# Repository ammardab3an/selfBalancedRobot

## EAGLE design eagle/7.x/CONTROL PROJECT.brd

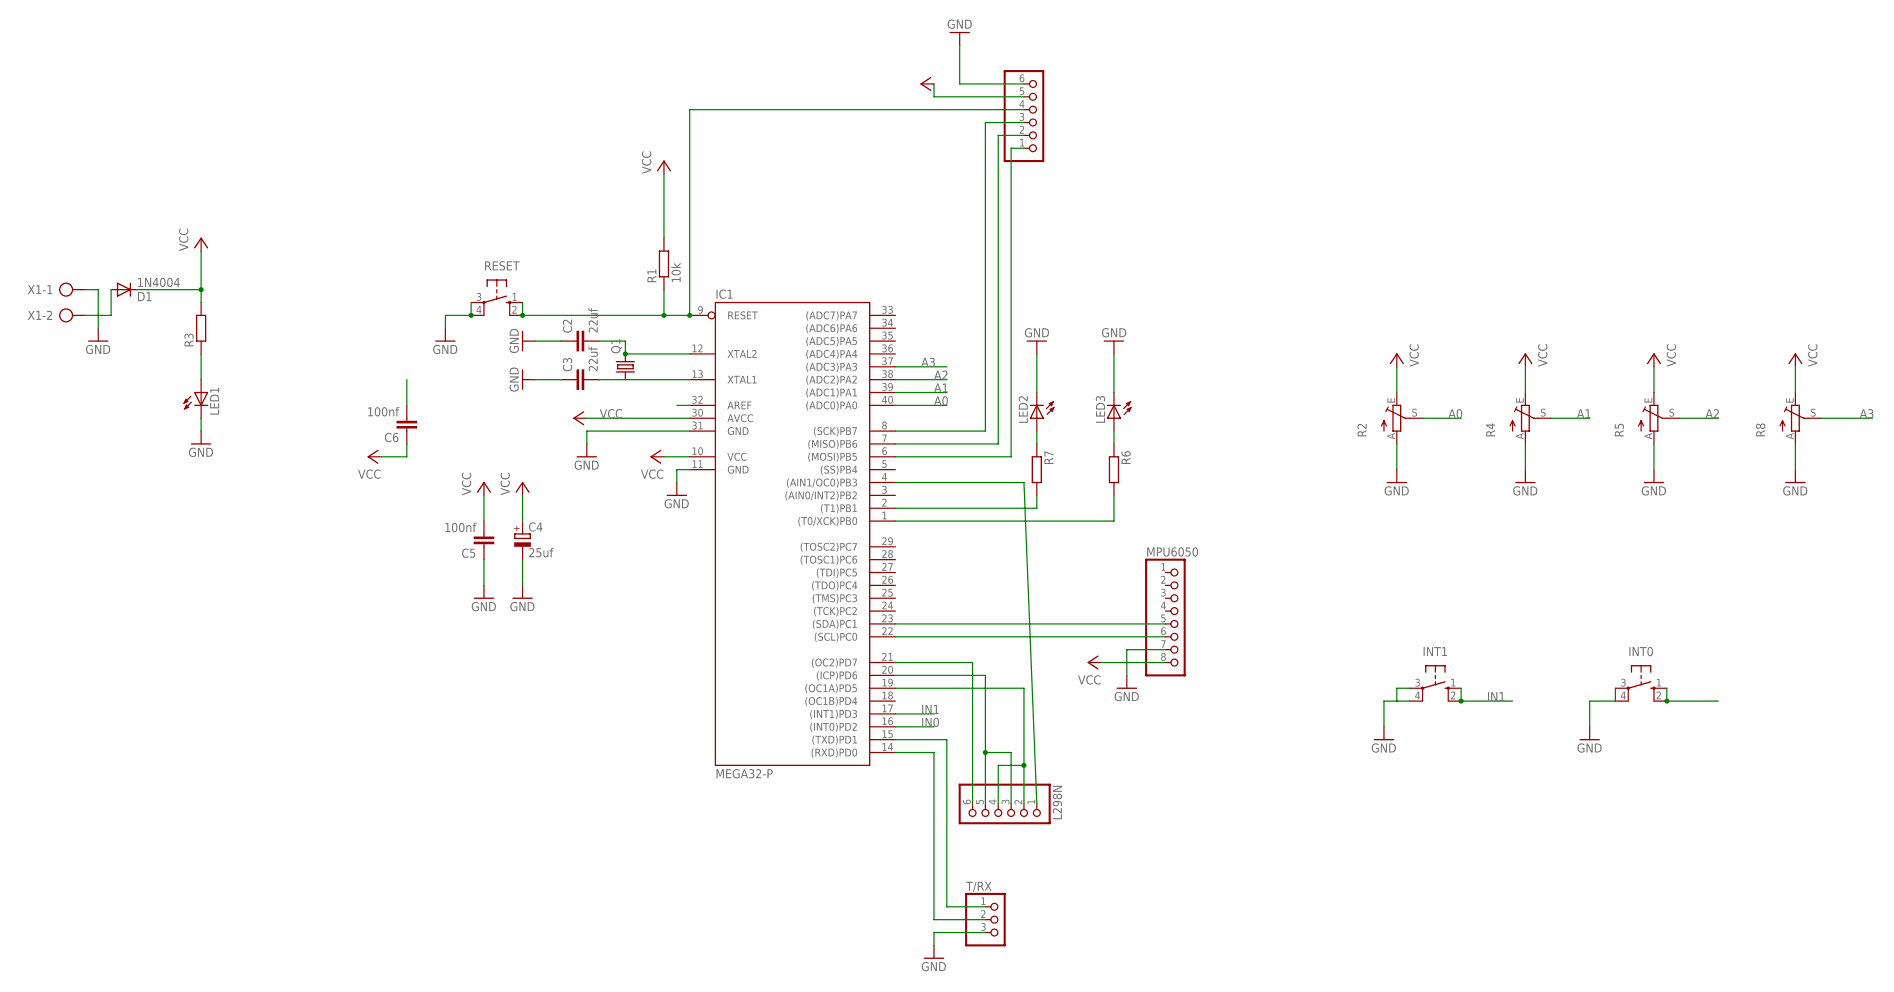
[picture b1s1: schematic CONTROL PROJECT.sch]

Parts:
C2, C3: 22uf; C050-025X075
C4: 25uf; E1,8-4
C5, C6: 100nf; C050-025X075
D1: 1N4004; DO41-10
IC1: MEGA32-P; DIL40
INT0, INT1: 10-XX; B3F-10XX
L298N: PINHD-1X6; 1X06
LED1, LED2, LED3: LED5MM
MPU6050: PINHD-1X8; 1X08
PROG: PINHD-1X6; 1X06
Q1: CRYSTALHC49U-V; HC49U-V
R1: 10k; 0207/7
R2, R4, R5, R8: TRIM_EU-RJ6; RJ6
R3, R6, R7: R-EU_0207/7; 0207/7
RESET: 10-XX; B3F-10XX
T/RX: PINHD-1X3; 1X03
X1: AK300/2

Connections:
A0: IC1.40 ((ADC0)PA0), R2.S
A1: IC1.39 ((ADC1)PA1), R4.S
A2: IC1.38 ((ADC2)PA2), R5.S
A3: IC1.37 ((ADC3)PA3), R8.S
AREF: C6.2, IC1.32 (AREF)
GND: C2.1, C3.1, C4.-, C5.1, IC1.11 (GND), IC1.31 (GND), INT0.3, INT0.4 (P1), INT1.3, INT1.4 (P1), LED1.K (C), LED2.K (C), LED3.K (C), MPU6050.7, PROG.6, R2.A, R4.A, R5.A, R8.A, RESET.3, RESET.4 (P1), T/RX.3, X1.1
IN0: IC1.16 ((INT0)PD2), INT0.1 (S), INT0.2 (S1)
IN1: IC1.17 ((INT1)PD3), INT1.1 (S), INT1.2 (S1)
MISO: IC1.7 ((MISO)PB6), PROG.2
MOSI: IC1.6 ((MOSI)PB5), PROG.1
unnamed: C2.2, IC1.12 (XTAL2), Q1.2
unnamed: C3.2, IC1.13 (XTAL1), Q1.1
unnamed: IC1.2 ((T1)PB1), R7.2
unnamed: LED1.A, R3.1
unnamed: D1.A, X1.2
unnamed: IC1.1 ((T0/XCK)PB0), R6.2
unnamed: LED3.A, R6.1
unnamed: LED2.A, R7.1
unnamed: IC1.19 ((OC1A)PD5), L298N.2, L298N.4
unnamed: IC1.20 ((ICP)PD6), L298N.3, L298N.5
OC0: IC1.4 ((AIN1/OC0)PB3), L298N.1
OC2: IC1.21 ((OC2)PD7), L298N.6
RESET: IC1.9 (RESET), PROG.4, R1.1, RESET.1 (S), RESET.2 (S1)
RX: IC1.14 ((RXD)PD0), T/RX.2
SCK: IC1.8 ((SCK)PB7), PROG.3
SCL: IC1.22 ((SCL)PC0), MPU6050.6
SDA: IC1.23 ((SDA)PC1), MPU6050.5
TX: IC1.15 ((TXD)PD1), T/RX.1
VCC: C4.+, C5.2, C6.1, D1.C, IC1.10 (VCC), IC1.30 (AVCC), MPU6050.8, PROG.5, R1.2, R2.E, R3.2, R4.E, R5.E, R8.E

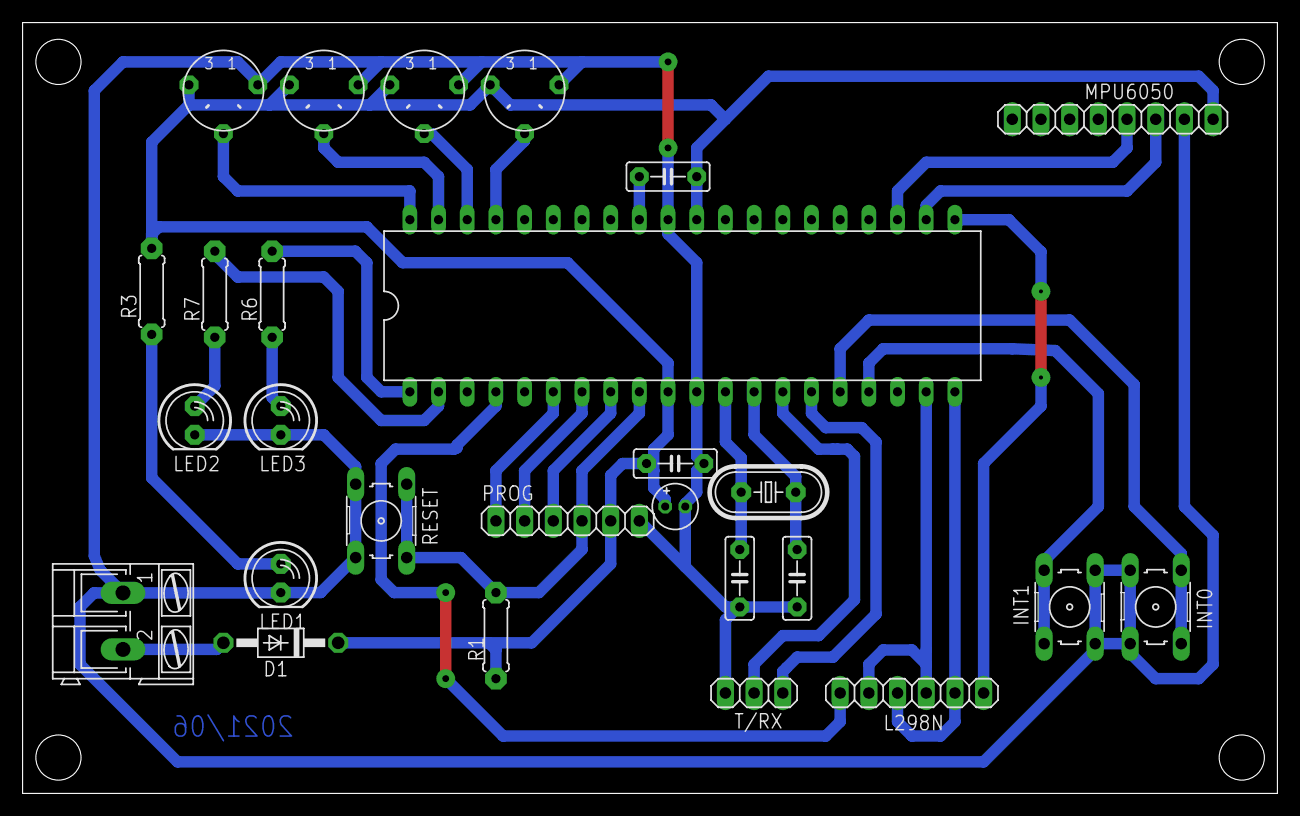
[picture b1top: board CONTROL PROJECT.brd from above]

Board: 2 copper layers, 111.1 x 68.2 mm, 27 parts (0 on the bottom side), 29 nets.

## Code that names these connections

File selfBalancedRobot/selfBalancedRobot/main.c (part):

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{
	TCNT0 = 0x00;
	TCNT2 = 0X00;
	DDRB |= 1 << PB3;
	DDRD |= 1 << PD7;
}

void PWM_Start()
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int main()
{
	
	DDRB |= (1<<PB0) | (1<<PB1);
	DDRD |= (1<<PD5) | (1<<PD6);
	
	I2C_Init();
	USART_Init(57600);
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		
		if(!go_flag || (pitch > 50) || (pitch < -50) || (roll > 50) || (roll < -50)){
			PWM_SetDutyCycle(0);
			PORTB |= (1<<PB1);
			PORTB &= ~(1<<PB0);
		}
		else{
			
			PORTB |= (1<<PB0);
			PORTB &= ~(1<<PB1);
			
			sum_error += error * dt;

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
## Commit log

2021-05-17 adding schematic
2021-06-05 backup
2021-06-25 final
2024-01-06 gallery
